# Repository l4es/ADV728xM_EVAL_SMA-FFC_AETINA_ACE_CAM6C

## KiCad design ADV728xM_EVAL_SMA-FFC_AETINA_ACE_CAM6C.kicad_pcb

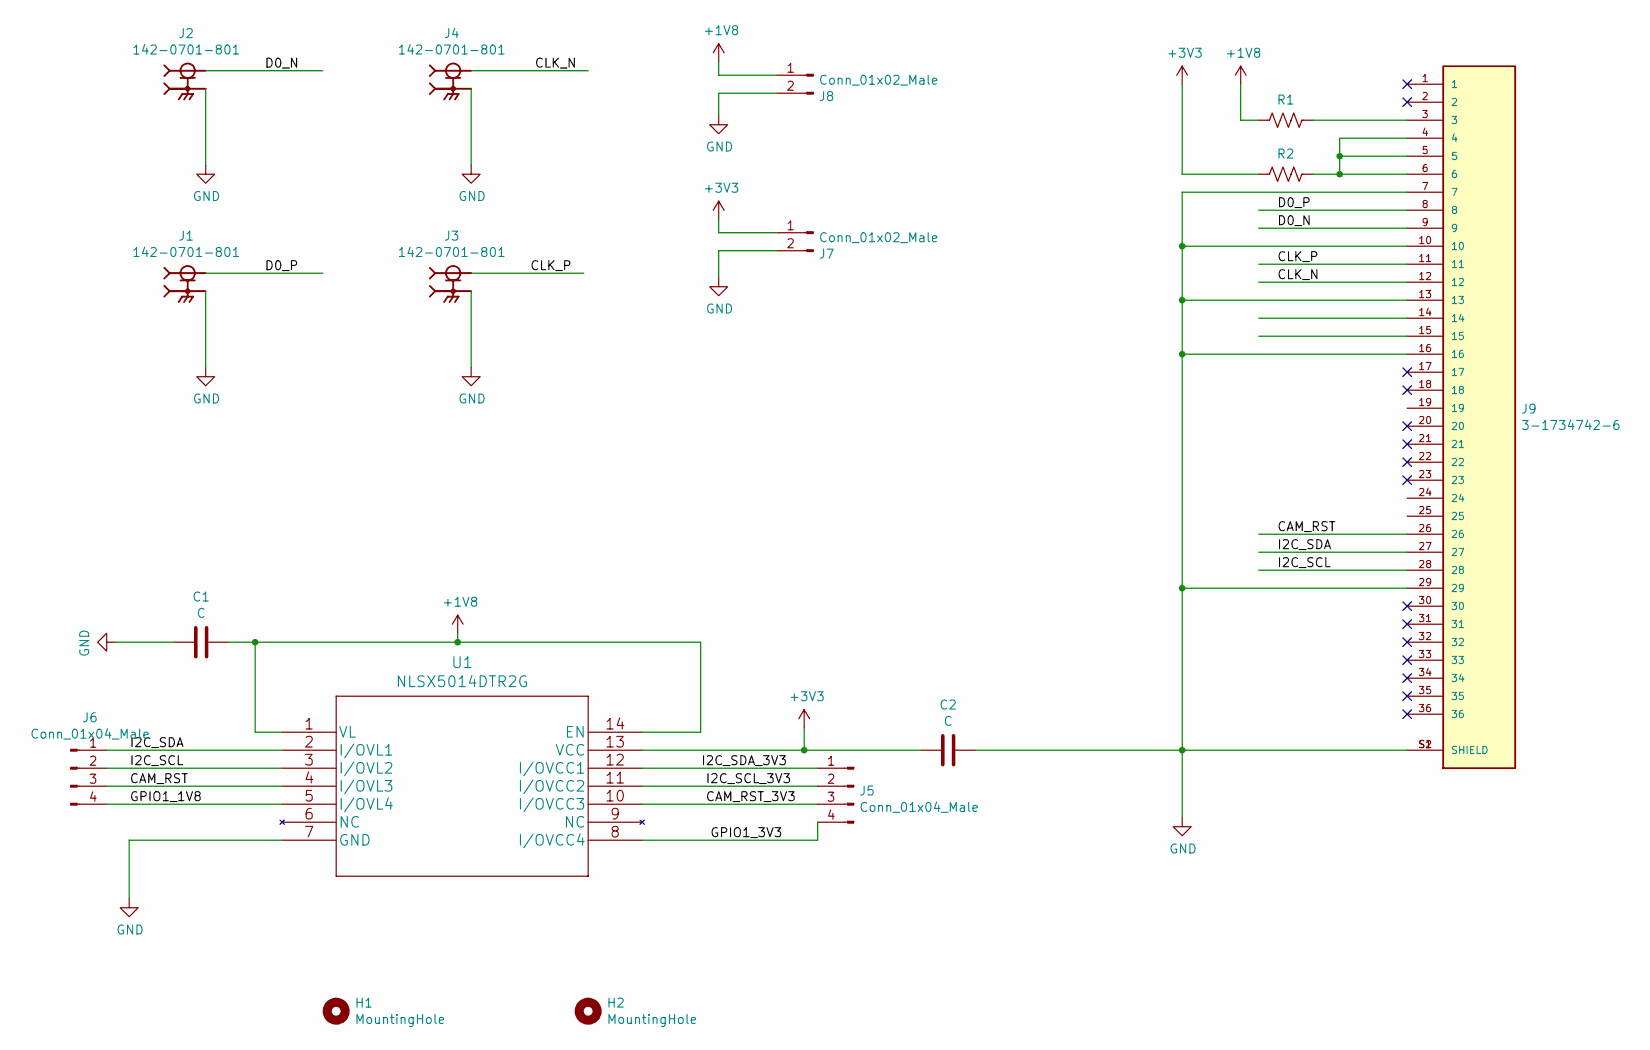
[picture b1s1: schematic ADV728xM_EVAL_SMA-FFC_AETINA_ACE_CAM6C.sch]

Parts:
C1, C2: C; C_0603_1608Metric_Pad1.08x0.95mm_HandSolder
H1, H2: MountingHole; MountingHole_3.2mm_M3
J1, J2, J3, J4: 142-0701-801; CINCH_142-0701-801; PARTREV N/A
J5, J6: Conn_01x04_Male; PinHeader_1x04_P2.54mm_Vertical
J7, J8: Conn_01x02_Male; PinHeader_1x02_P2.54mm_Vertical
J9: 3-1734742-6; TE_3-1734742-6; PARTREV P
R1, R2: 0; R_0805_2012Metric_Pad1.20x1.40mm_HandSolder
U1: NLSX5014DTR2G

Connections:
+1V8: C1.2, J8.1, R1.2, U1.1 (VL), U1.14 (EN)
+3V3: C2.2, J7.1, R2.2, U1.13 (VCC)
/CAM_RST: J6.3, J9.26, U1.4 (I/OVL3)
/CAM_RST_3V3: J5.3, U1.10 (I/OVCC3)
/CLK_N: J4.1, J9.12
/CLK_P: J3.1, J9.11
/D0_N: J2.1, J9.9
/D0_P: J1.1, J9.8
/GPIO1_1V8: J6.4, U1.5 (I/OVL4)
/GPIO1_3V3: J5.4, U1.8 (I/OVCC4)
/I2C_SCL: J6.2, J9.28, U1.3 (I/OVL2)
/I2C_SCL_3V3: J5.2, U1.11 (I/OVCC2)
/I2C_SDA: J6.1, J9.27, U1.2 (I/OVL1)
/I2C_SDA_3V3: J5.1, U1.12 (I/OVCC1)
GND: C1.1, C2.1, J1.S1, J1.S2, J1.S3, J1.S4, J2.S1, J2.S2, J2.S3, J2.S4, J3.S1, J3.S2, J3.S3, J3.S4, J4.S1, J4.S2, J4.S3, J4.S4, J7.2, J8.2, J9.7, J9.10, J9.13, J9.16, J9.29, J9.S1 (SHIELD), J9.S2 (SHIELD), U1.7 (GND)
unnamed: J9.3, R1.1
unnamed: J9.4, J9.5, J9.6, R2.1

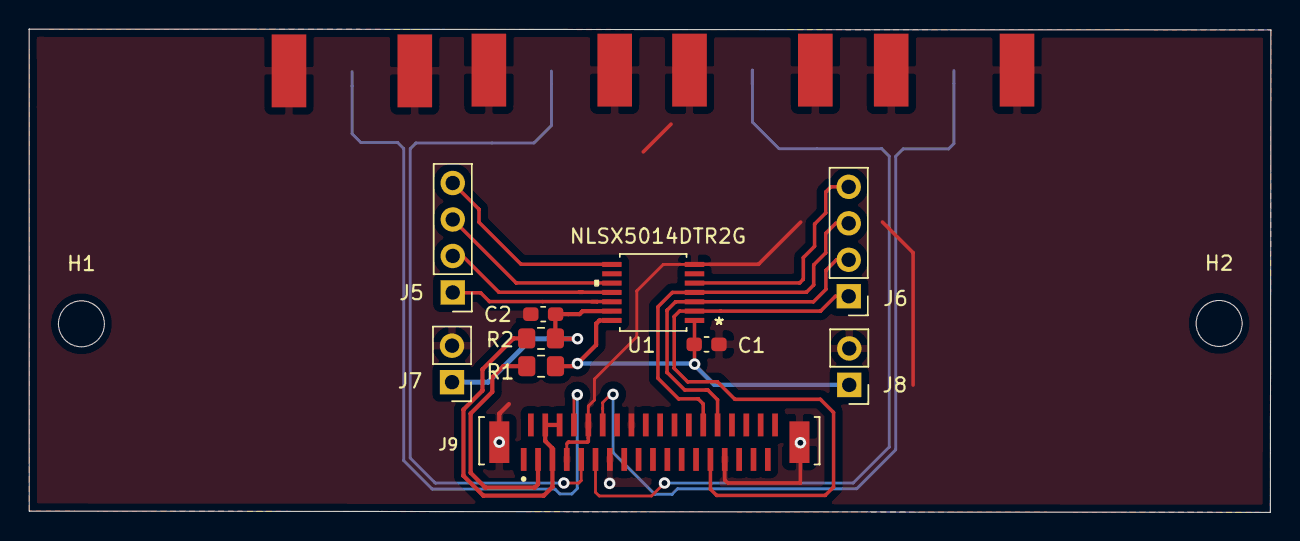
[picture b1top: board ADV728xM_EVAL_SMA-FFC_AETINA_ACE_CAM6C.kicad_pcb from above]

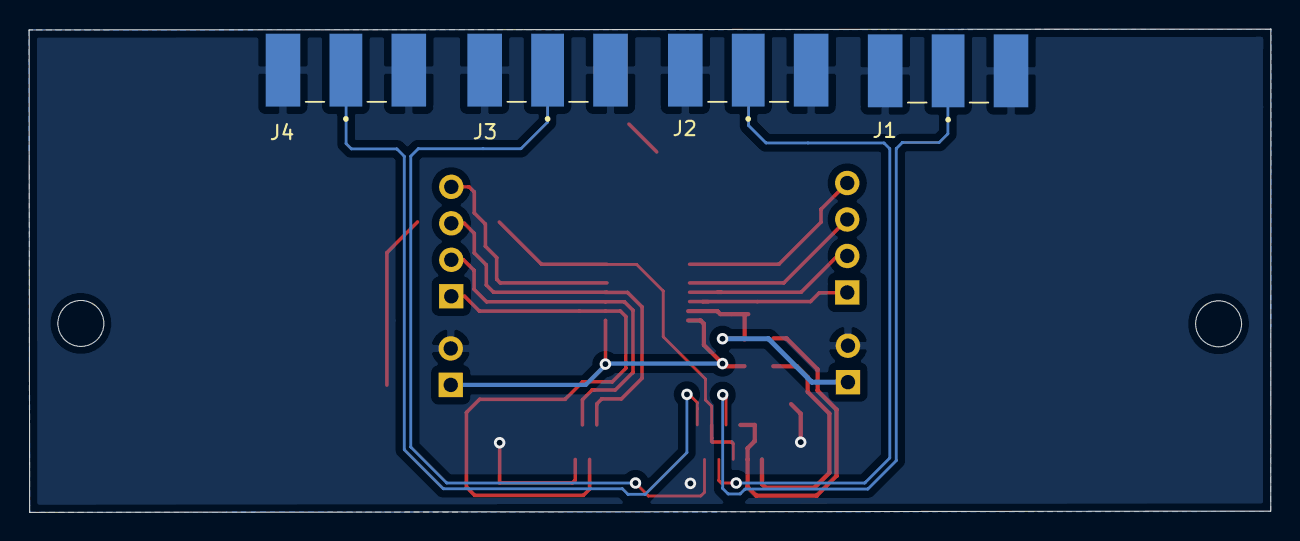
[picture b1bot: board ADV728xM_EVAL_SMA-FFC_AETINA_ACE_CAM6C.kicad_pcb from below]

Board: 2 copper layers, 86.5 x 33.7 mm, 16 parts (4 on the bottom side), 17 nets.

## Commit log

2021-07-26 Add production release V1A
2021-07-26 Add production release V1A with board outline
2021-08-07 Move SMA connetors to back layer

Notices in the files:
parts and their libraries:
Copyright 2021 Accelerated Designs. All rights reserved.
